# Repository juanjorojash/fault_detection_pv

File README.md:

# Embedded fault detection in PV modules usign electrical variables

## Acronyms ##
* **MCU:** microcontroller unit
* **MPU:** microprocessor unit 
* **EFS:** embedded fault detection system
* **CFS:** centralized faul detection system
* **PV:** photovoltaic

## Key features
* MCU: **MSP432** in a [MSP432P401R](http://www.ti.com/tool/MSP-EXP432P401R) for embedded detection algorithm implementation and communication with CPU. 
    * Programming language: **C**
* MPU: **Cortex-A72 (ARM v8-A)** in a [Raspberry Pi 4](https://www.raspberrypi.org/products/raspberry-pi-4-model-b/) for central data collection and higher level detection algorithm
    * Programming language: **Python**
* Hardware schematics: **EAGLE**

## What is the purpose of this project?
This project is about fault detection usign a combination of an EFS that can be connected close to the PV module and a CFS that will receive the data from several EFS to implement a higher level fault detection.  

## What does the MCU do?
The MCU conducts all I,V measurements in the PV module and use those measurements to detect fault by usign one or several algorithms. After finishing the analysis the MCU sends the data to the MPU. 

## What does the MPU do?
The MPU receive the data from several MCUs and performs a higher level algorithm for fault detection and fault location. 

## What about the hardware?
The **EFS prototype board** has been adapted to carry the [MSP432P401R LaunchPad](http://www.ti.com/tool/MSP-EXP432P401R), a development kit from Texas Instruments that holds the MSP432.
The advantage of using the LaunchPad instead of a naked MSP432 is being able to make use of already existing circuitry around the MPS432,
such as an appropriate power supply in addition to an on-board debugger and a backchannel UART.

## Known issues
* Not yet

## What does this repository contain?
<!-- * **C code Master MCU**: MSP432 - I,V measurements in EPS + MPPT + sending desired duty cycle to µC slaves via SPI
* **C code Slave MCUs**: PIC16F - reception of desired duty cycle via SPI from µC master + PWM generation, setting duty cycle
* **Hardware schematics**: BDC prototype board v2.3, adapted for conducting MPPT -->

## Who can I talk to?
* [Juan J. Rojas](mailto:juan.rojas@tec.ac.cr)
* [Luis D. Murillo](mailto:lmurillo@tec.ac.cr)

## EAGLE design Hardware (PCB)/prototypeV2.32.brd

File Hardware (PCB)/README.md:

# Hardware (PCB)

## Description
The **BDC prototype board** (v2.3) is based on a previous work of [Juan J. Rojas](mailto:juan.rojas@itcr.ac.cr).
It has been adapted to carry the [MSP432P401R LaunchPad](http://www.ti.com/tool/MSP-EXP432P401R), a development kit from Texas Instruments that holds the MSP432.
The advantage of using the LaunchPad instead of a naked MSP432 is being able to make use of already existing circuitry around the MPS432,
such as an appropriate power supply in addition to an on-board debugger and a backchannel UART.

## Known issues
### 5 V bus on PCB
The PCB 5 V bus can be powered by three different voltage sources:
* **5 V extern** - **[recommended]** using the 7.5 VDC power jack as input, the 5 V bus is powered through a 7805 linear regulator. Select through jumper `5V_EXT`.  
  Recommended, since the 7.5 VDC extern are **always used** in order to power the reference voltages [REF195](https://www.analog.com/en/products/ref195.html#product-overview)
  for the current sensors [ACS723](https://www.allegromicro.com/en/Products/Sense/Current-Sensor-ICs/Zero-To-Fifty-Amp-Integrated-Conductor-Sensor-ICs/ACS723).
* **5 V intern** - using the 5 V power distribution unit on the PCB to power the 5 V bus. Select through jumper `5V_INT`
* **5 V from LaunchPad** - using the USB 5V from the LaunchPad to power the 5 V bus. Select through jumper `J101 5V` on LaunchPad.

Only one of the three above-mentioned jumpers can be plugged in at the same time!

## Workarounds
### 5 V bus on PCB
* In the _current state of the PCB design_, **always remove the J101 5V jumper** (J101 jumper bench on MSP432 LaunchPad)!  
  Otherwise, two different power supplies will feed the PCB 5V bus: 5V from USB **and** 5V from either _PCB intern_ (from PDU5V) or _PCB extern_ (7.5V in -> linear voltage regulator to 5V)  
  However, *USB must be connected* in order to feed the MSP432 with 3.3V (voltage regulator from 5V to 3.3V is on LaunchPad and cannot be powered by 5V bus)
* The pins for ADC reference voltage should have **two decoupling capacitors, 5 µF and 50 nF**. However, the current design of the PCB does not have those capacitors. They might be added by another small PCB to plug ontop of the LaunchPad.

### Power MSP432 through PCB-internal 3.3V power source
MSP432 _can_ be fed through PCB internal 3.3V from **PDU3.3V**. Not recommended. Do this only, when 3.3V supply from LaunchPad is not desired to power the MSP432!
* Remove **J101 3V jumper** (J101 jumper bench on MSP432 LaunchPad)
* **Activate PDU3.3V** through jumper on PCB and **connect 3.3V pin on MSP432 LaunchPad** through a cable to PDU3.3V_out
* Removal of **J101 3V jumper** is important! Otherwise, two different power supplies would feed the same 3.3V bus
 
## Who can I talk to?
* [Adrian Wenzel](mailto:a.wenzel@tum.de) 
* [Juan J. Rojas](mailto:juan.rojas@itcr.ac.cr)

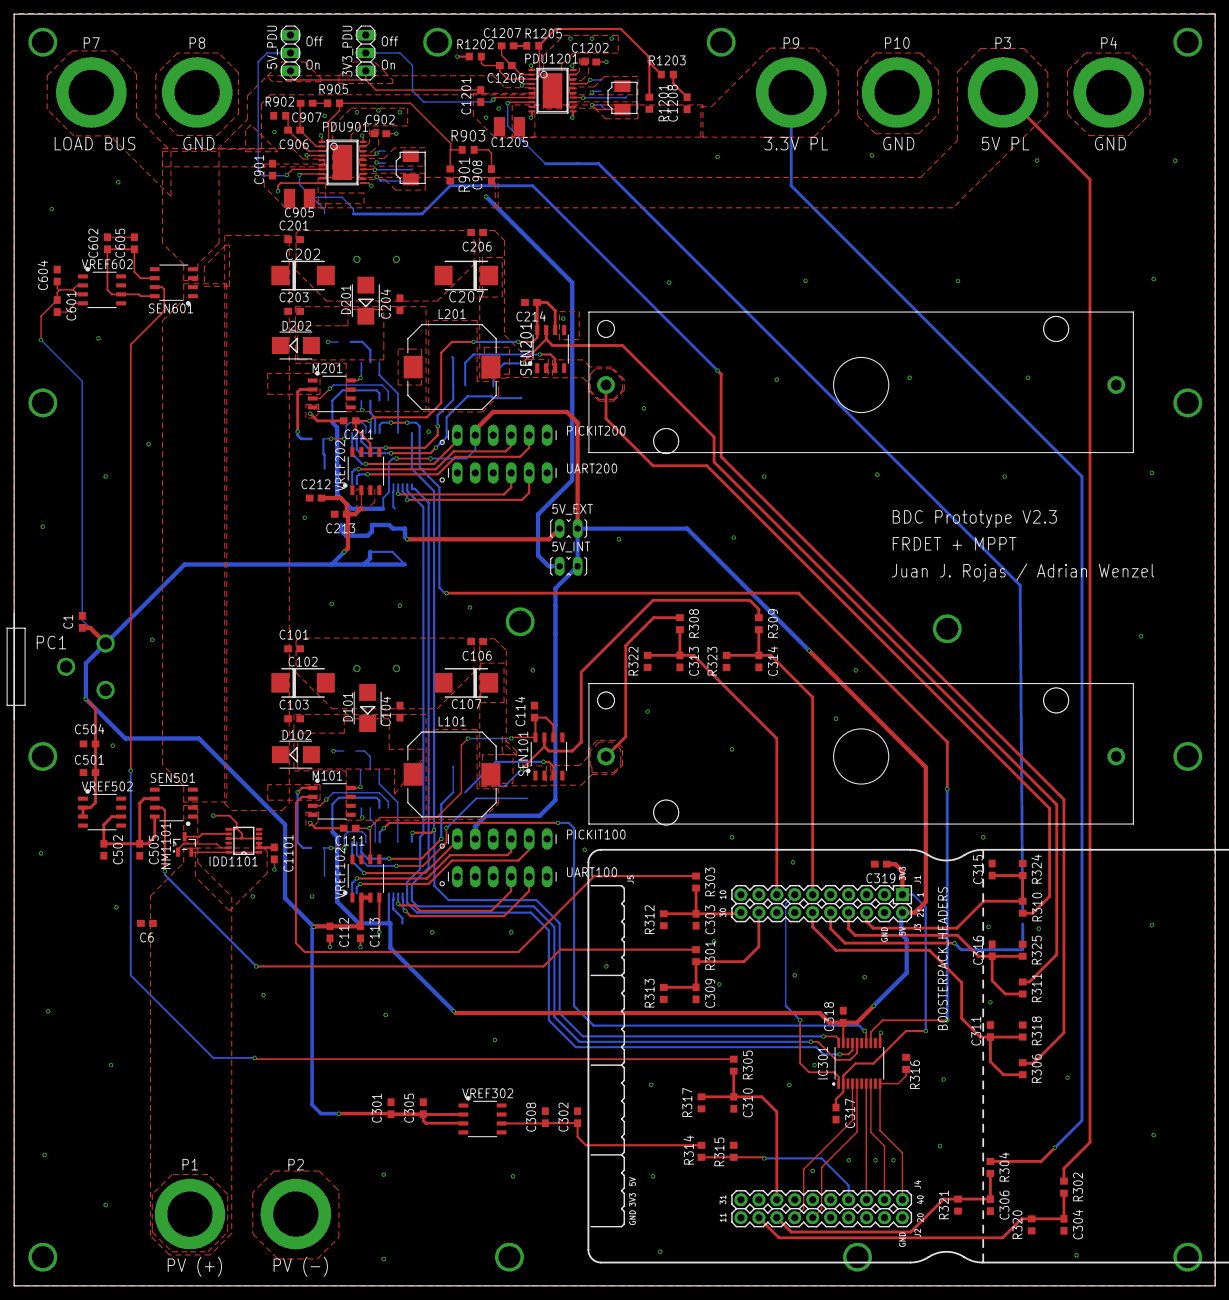
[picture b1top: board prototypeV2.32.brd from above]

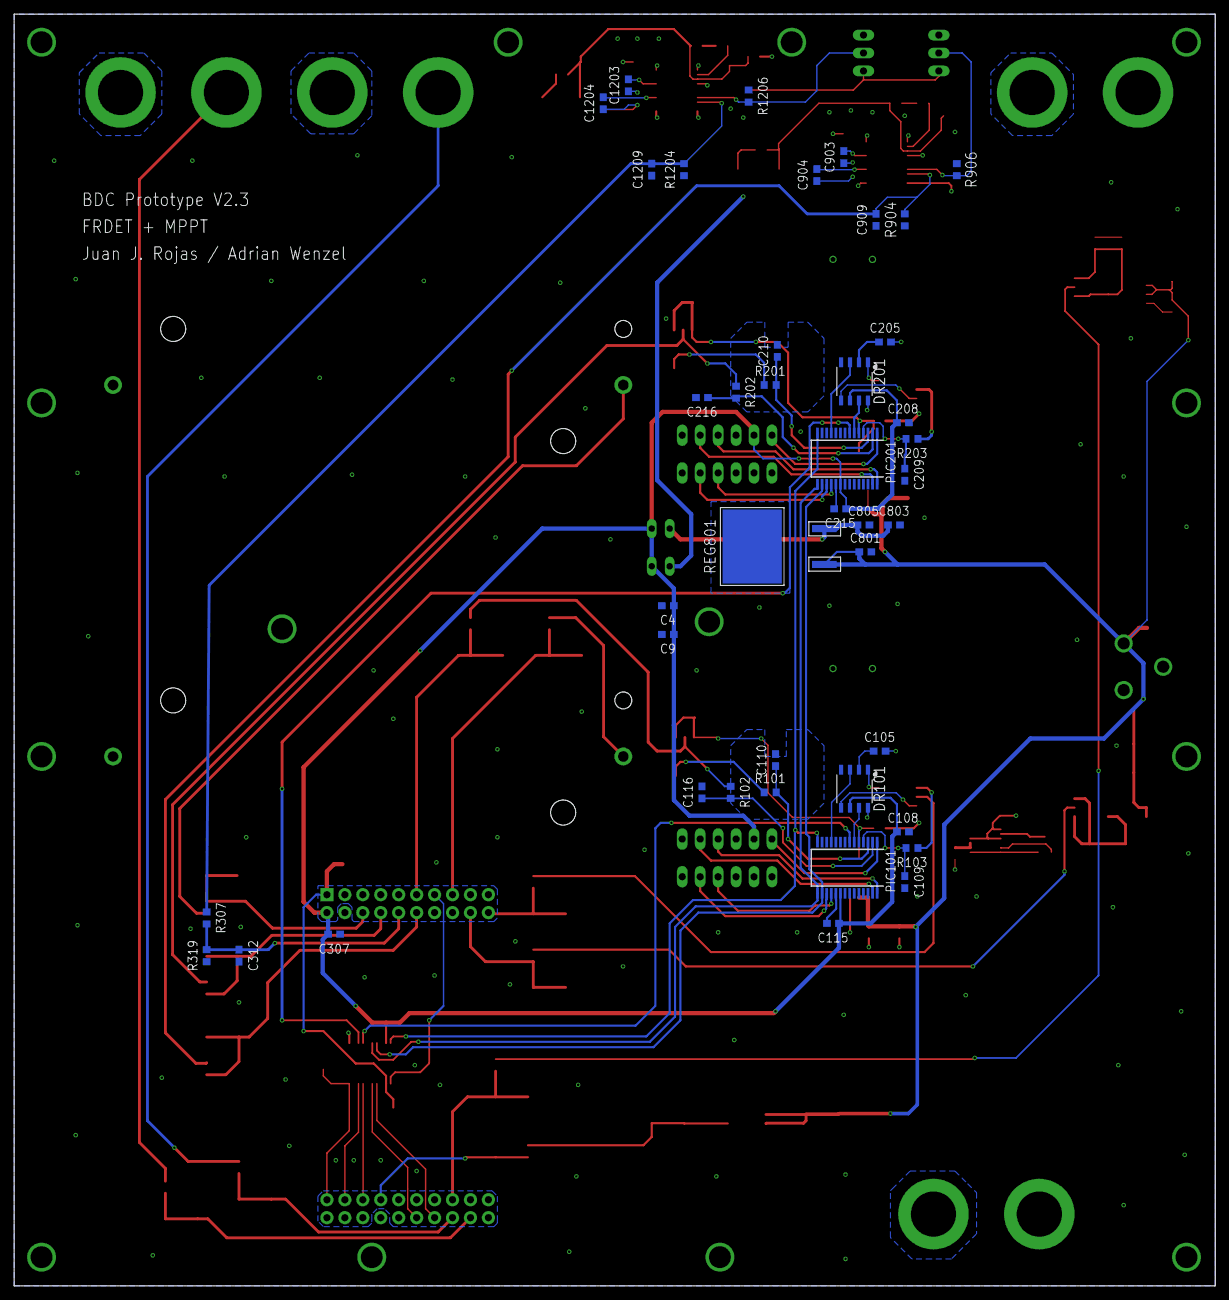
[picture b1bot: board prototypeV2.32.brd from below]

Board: 2 copper layers, 170.0 x 180.0 mm, 177 parts (42 on the bottom side), 99 nets.

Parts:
3V3_PDU, 5V_PDU: 1X03
5V_EXT, 5V_INT: J2P
C1, C9, C112, C212, C301, C501, C601, C805, C901: 10u; C0603
C4, C109, C110, C114, C115, C209, C210, C214, C215, C307, C308, C317, C318, C319, C505, C605, C903, C904, C1101, C1203, C1204: 0.1u; C0603
C6, C101, C105, C106, C111, C113, C201, C205, C206, C211, C213, C302, C305, C502, C504, C602, C604, C803, C902, C1202: 1u; C0603
C102, C107, C202, C207: 33u; C7343
C103, C104, C116, C203, C204, C216: 1n; C0603
C108, C208: 2.2u; C0603
C303, C304, C306, C309, C310, C311, C312, C313, C314, C315, C316: 1.2n; C0603
C801: 0.33u; C0603
C905, C1205: 47u; C1210
C906: 22p; C0603
C907: 680p; C0603
C908: 47p; C0603
C909, C1209: 100p; C0603
C1201: 22u; C0603
C1206: 15p; C0603
C1207: 820p; C0603
C1208: 56p; C0603
CELL1, CELL2: CELL18650_HOLDER; 18650_HOLDER
D101, D102, D201, D202: BAQ133; SMB
DR101, DR201: TPS28225D; SOIC-8
IC301: TXS0108E; SOP65P640X120-20
IDD1101: LTC4352CMS; MSOP12
JP301: BOOSTERPACK_HEADERS
L101, L201: 22u; CLF12555
L901, L1201: 4.7u; SPM4020T
M101, M201: SI4914BDY; SOIC-8
NM1101: IRLML6244TRPBF; SOT-23
P1, P2, P3, P4, P7, P8, P9, P10: TJ-563
PC1: 722RA
PDU901, PDU1201: LTC3112EFE; TSSOP20CA
PIC101, PIC201: PIC16F1786-I/SS; SSOP28
PICKIT100, PICKIT200: MA06-1
R101, R103, R201, R203: 200; R0603
R102, R202: 0; R0603
R301, R304, R305, R306, R307, R308, R309, R310, R311, R314: 12.4k; R0603
R302, R303, R312, R313, R315, R317, R318, R319, R320, R321, R322, R323, R324, R325: 23.2k; R0603
R316, R903, R906, R1206: 10k; R0603
R901: 845k; R0603
R902: 158k; R0603
R904, R1204: 42.2k; R0603
R905: 33k; R0603
R1201: 620k; R0603
R1202: 200k; R0603
R1203: 9.1k; R0603
R1205: 39k; R0603
REG801: NCV7805BD2TG; D2PAK-3
SEN101, SEN201, SEN501, SEN601: ACS723-05AB-T; SOIC-8
UART100, UART200: MA06-1
VREF102, VREF202, VREF302, VREF502, VREF602: REF195GSZ; SOIC-8

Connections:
3.3V_PL: C1205.1, C1208.1, P9.P, PDU1201.9, R304.1, R1201.2
5V_EXT: 5V_EXT.1, C803.1, C805.1, REG801.3
5V_ON: 5V_PDU.2, PDU901.7, R906.2
5V_PL: 5V_INT.1, C905.1, C908.1, P3.P, PDU901.9, R302.1, R901.2
7.5V: C1.1, C112.1, C113.1, C212.1, C213.1, C301.1, C305.1, C501.1, C504.1, C601.1, C604.1, C801.1, PC1.PIN, REG801.1, VREF102.2, VREF102.3, VREF202.2, VREF202.3, VREF302.2, VREF302.3, VREF502.2, VREF502.3, VREF602.2, VREF602.3
12V_ON: 3V3_PDU.2, PDU1201.7, R1206.2
!SPI_SS1: IC301.14, PIC101.7
!SPI_SS2: IC301.13, PIC201.7
+5V: 5V_EXT.2, 5V_INT.2, C4.1, C9.1, C108.1, C115.1, C208.1, C215.1, C307.1, C318.1, DR101.6, DR201.6, IC301.19, JP301.+5V, PIC101.20, PIC201.20, PICKIT100.2, PICKIT200.2
CONTROL:3V3: C317.1, C319.1, IC301.2, JP301.+3V3
CONTROL:3V3_REF: JP301.P5.6, R314.1, R315.2
CONTROL:5V_REF: C302.1, C308.1, R314.2, VREF302.6
CONTROL:!SS1: IC301.7, JP301.P2.4
CONTROL:!SS2: IC301.8, JP301.P2.6
CONTROL:CLK: IC301.1, JP301.P1.5
CONTROL:I_BAT1: C314.1, JP301.P4.3, R309.2, R323.2
CONTROL:I_BAT2: C316.1, JP301.P4.0, R311.2, R325.2
CONTROL:I_LOAD: C310.1, JP301.P5.1, R305.2, R317.2
CONTROL:I_PDU_3.3V: C312.1, JP301.P4.2, R307.2, R319.2
CONTROL:I_PDU_5V: C311.1, JP301.P4.4, R306.2, R318.2
CONTROL:I_PV: C309.1, JP301.P5.4, R301.2, R313.2
CONTROL:MISO: IC301.4, JP301.P1.7
CONTROL:MOSI: IC301.5, JP301.P1.6
CONTROL:OE_SPI: IC301.10, JP301.P2.7, R316.2
CONTROL:V_BAT1: C313.1, JP301.P4.6, R308.2, R322.2
CONTROL:V_BAT2: C315.1, JP301.P6.1, R310.2, R324.2
CONTROL:V_BUS: C303.1, JP301.P5.5, R303.2, R312.2
CONTROL:V_PDU_3.3V: C306.1, JP301.P5.0, R304.2, R321.2
CONTROL:V_PDU_5V: C304.1, JP301.P5.2, R302.2, R320.2
CONV1:5V_REF: C111.1, C114.1, PIC101.5, SEN101.6, SEN101.8, VREF102.6
CONV1:DR_EN: DR101.7, PIC101.6
CONV1:G1: DR101.1, M101.8
CONV1:G2: DR101.5, M101.3
CONV1:ICSPCLK: PIC101.27, PICKIT100.5
CONV1:ICSPDAT: PIC101.28, PICKIT100.4
CONV1:I_BAT: C116.1, PIC101.2, R102.2
CONV1:LO: C106.1, C107.+, L101.2, SEN101.1, SEN101.2
CONV1:MCLR: PIC101.1, PICKIT100.1
CONV1:N$2: C105.1, DR101.2
CONV1:PWM: DR101.3, PIC101.11
CONV1:RX: PIC101.18, UART100.4
CONV1:SW: C103.2, C104.1, C105.2, D101.C, D102.A, DR101.8, L101.1, M101.5, M101.6, M101.7
CONV1:TX: PIC101.17, UART100.5
CONV1:V_BAT: C110.1, PIC101.3, R101.2
CONV1:V_BUS: C109.1, PIC101.4, R103.2
CONV2:5V_REF: C211.1, C214.1, PIC201.5, SEN201.6, SEN201.8, VREF202.6
CONV2:DR_EN: DR201.7, PIC201.6
CONV2:G1: DR201.1, M201.8
CONV2:G2: DR201.5, M201.3
CONV2:ICSPCLK: PIC201.27, PICKIT200.5
CONV2:ICSPDAT: PIC201.28, PICKIT200.4
CONV2:I_BAT: C216.1, PIC201.2, R202.2
CONV2:LO: C206.1, C207.+, L201.2, SEN201.1, SEN201.2
CONV2:MCLR: PIC201.1, PICKIT200.1
CONV2:N$2: C205.1, DR201.2
CONV2:PWM: DR201.3, PIC201.11
CONV2:RX: PIC201.18, UART200.4
CONV2:SW: C203.2, C204.1, C205.2, D201.C, D202.A, DR201.8, L201.1, M201.5, M201.6, M201.7
CONV2:TX: PIC201.17, UART200.5
CONV2:V_BAT: C210.1, PIC201.3, R201.2
CONV2:V_BUS: C209.1, PIC201.4, R203.2
GND: 3V3_PDU.1, 5V_PDU.1, C1.2, C4.2, C6.2, C9.2, C101.2, C102.-, C104.2, C106.2, C107.-, C108.2, C109.2, C110.2, C111.2, C112.2, C113.2, C114.2, C115.2, C116.2, C201.2, C202.-, C204.2, C206.2, C207.-, C208.2, C209.2, C210.2, C211.2, C212.2, C213.2, C214.2, C215.2, C216.2, C301.2, C302.2, C303.2, C304.2, C305.2, C306.2, C307.2, C308.2, C309.2, C310.2, C311.2, C312.2, C313.2, C314.2, C315.2, C316.2, C317.2, C318.2, C319.2, C501.2, C502.2, C504.2, C505.2, C601.2, C602.2, C604.2, C605.2, C801.2, C803.2, C805.2, C901.2, C902.2, C905.2, C909.1, C1101.2, C1201.2, C1202.2, C1205.2, C1209.1, CELL1.BB1.N, CELL2.BB1.N, D101.A, D201.A, DR101.4, DR201.4, IC301.11, IDD1101.4, IDD1101.7, IDD1101.9, JP301.GND, JP301.P5.7, M101.4, M201.4, P2.P, P4.P, P8.P, P10.P, PC1.SLEEVE, PC1.SLEEVE_SHUNT, PDU901.1, PDU901.4, PDU901.10, PDU901.11, PDU901.20, PDU901.21, PDU1201.1, PDU1201.4, PDU1201.10, PDU1201.11, PDU1201.20, PDU1201.21, PIC101.8, PIC101.19, PIC201.8, PIC201.19, PICKIT100.3, PICKIT200.3, R312.1, R313.1, R315.1, R316.1, R317.1, R318.1, R319.1, R320.1, R321.1, R322.1, R323.1, R324.1, R325.1, R902.1, R904.1, R906.1, R1202.1, R1204.1, R1206.1, REG801.4, SEN101.5, SEN201.5, SEN501.5, SEN601.5, UART100.1, UART200.1, VREF102.4, VREF202.4, VREF302.4, VREF502.4, VREF602.4
IDEAL_D1:N$1: IDD1101.11, NM1101.1
IDEAL_D1:N$4: C1101.1, IDD1101.2, IDD1101.3
IS_BAT1: R102.1, R309.1, SEN101.7
IS_BAT2: R202.1, R311.1, SEN201.7
IS_LOAD: R305.1, SEN601.7
IS_PDU_3.3V: C1209.2, PDU1201.8, R307.1, R1204.2
IS_PDU_5V: C909.2, PDU901.8, R306.1, R904.2
IS_PV: R301.1, SEN501.7
LOAD_BUS: 3V3_PDU.3, 5V_PDU.3, C901.1, C1201.1, P7.P, PDU901.5, PDU901.6, PDU1201.5, PDU1201.6, SEN601.3, SEN601.4
unnamed: IDD1101.8, NM1101.3, SEN501.1, SEN501.2
PDU_3.3V:N$1: C1203.2, PDU1201.17
PDU_3.3V:N$2: C1202.1, PDU1201.18, PDU1201.19
PDU_3.3V:N$3: C1204.2, PDU1201.14
PDU_3.3V:N$4: C1203.1, L1201.1, PDU1201.15, PDU1201.16
PDU_3.3V:N$5: C1207.1, R1205.1
PDU_3.3V:N$6: C1206.1, C1207.2, PDU1201.2
PDU_3.3V:N$7: C1204.1, L1201.2, PDU1201.12, PDU1201.13
PDU_3.3V:N$8: C1208.2, R1203.2
PDU_3.3V:N$9: C1206.2, PDU1201.3, R1201.1, R1202.2, R1203.1, R1205.2
PDU_5V:N$1: C903.2, PDU901.17
PDU_5V:N$2: C902.1, PDU901.18, PDU901.19
PDU_5V:N$3: C904.2, PDU901.14
PDU_5V:N$4: C903.1, L901.1, PDU901.15, PDU901.16
PDU_5V:N$5: C907.1, R905.1
PDU_5V:N$6: C906.1, C907.2, PDU901.2
PDU_5V:N$7: C904.1, L901.2, PDU901.12, PDU901.13
PDU_5V:N$8: C908.2, R903.2
PDU_5V:N$9: C906.2, PDU901.3, R901.1, R902.2, R903.1, R905.2
PV: C6.1, IDD1101.1, IDD1101.12, NM1101.2, P1.P
PV_BUS: C101.1, C102.+, C103.1, C201.1, C202.+, C203.1, D102.C, D202.C, M101.1, M101.2, M201.1, M201.2, R103.1, R203.1, R303.1, SEN501.3, SEN501.4, SEN601.1, SEN601.2
SENS_LOAD:5V_REF: C602.1, C605.1, SEN601.6, SEN601.8, VREF602.6
SENS_PV:5V_REF: C502.1, C505.1, SEN501.6, SEN501.8, VREF502.6
SPI_MISO: IC301.17, PIC101.16, PIC201.16
SPI_MOSI: IC301.16, PIC101.15, PIC201.15
SPI_SCLK: IC301.20, PIC101.14, PIC201.14
VS_BAT1: CELL1.BB1.P, R101.1, R308.1, SEN101.3, SEN101.4
VS_BAT2: CELL2.BB1.P, R201.1, R310.1, SEN201.3, SEN201.4

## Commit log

2020-03-31 Initial commit
    Based on Adrian stuff
2020-04-02 Include project configuration in repository
2020-04-02 Include project files
